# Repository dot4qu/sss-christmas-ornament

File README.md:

# sss-christmas-ornament

A donut-shaped christmas ornament to share with friends and family in 2022. Hardware designed in KiCad, firmware written with Arduino framework and flashed over AVR UPDI interface.

More information in the writeup [here](https://brian.team/art/ornament-2022/).

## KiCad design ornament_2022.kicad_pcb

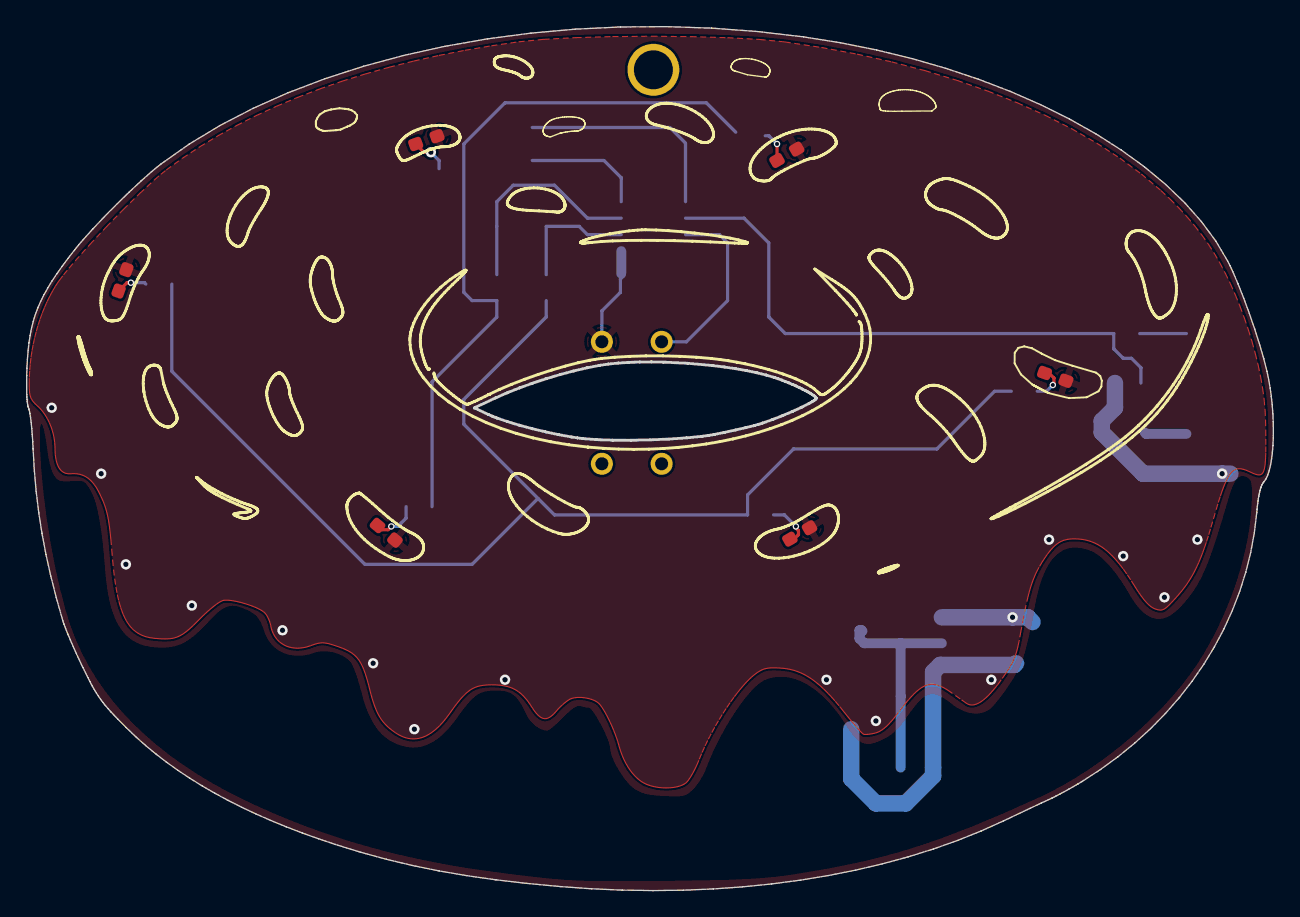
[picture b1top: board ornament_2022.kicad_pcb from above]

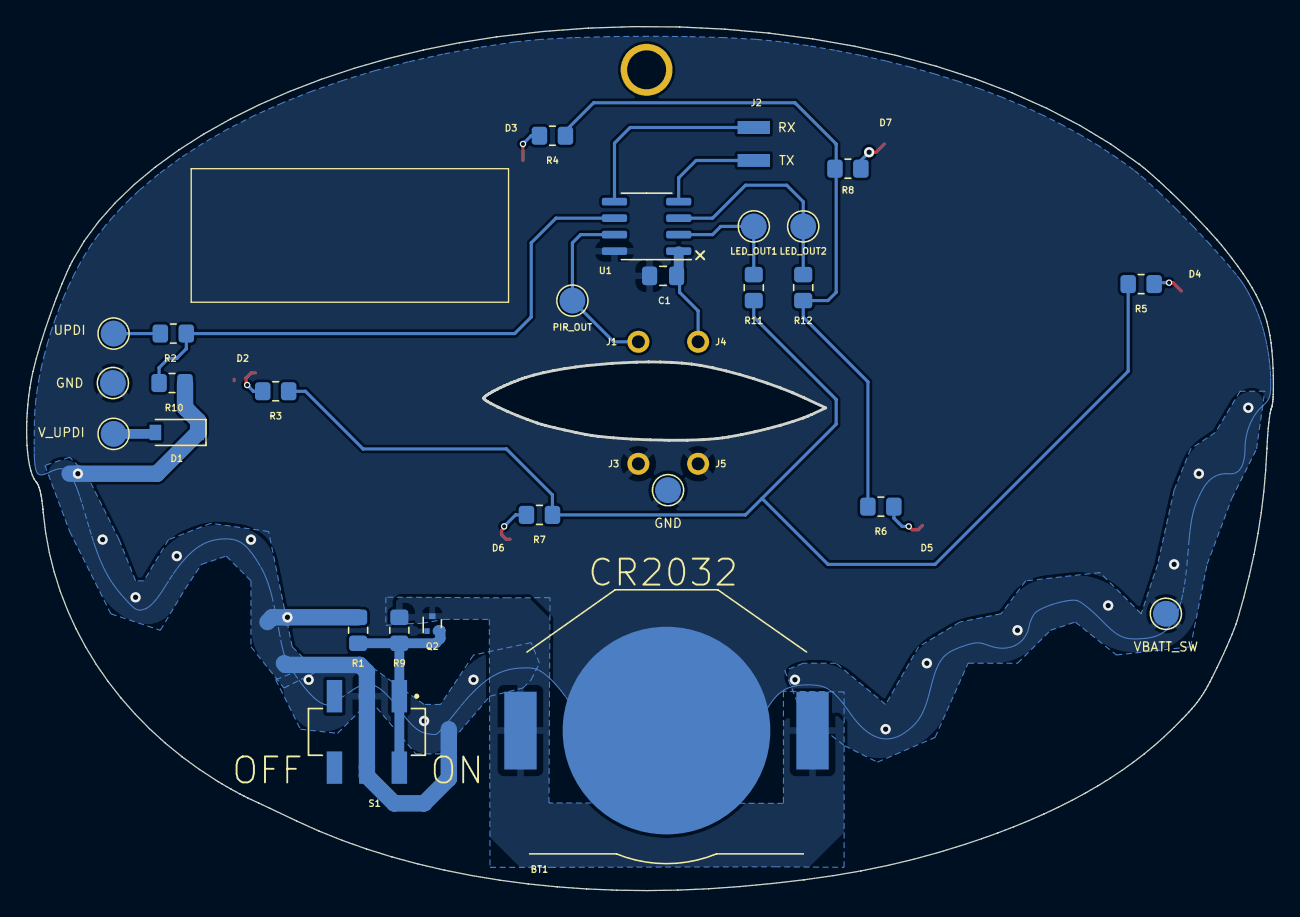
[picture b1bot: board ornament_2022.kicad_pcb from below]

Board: 2 copper layers, 95.9 x 66.4 mm, 37 parts (31 on the bottom side), 20 nets.

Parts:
BT1: CR2032; BatteryHolder_AdamTech_BH-67D-5_1x2032
C1: 0.1uF; C_0805_2012Metric_Pad1.18x1.45mm_HandSolder
D1: 1N4148W; D_SOD-123
D2, D3, D4, D5, D6, D7: LED; LED_0603_1608Metric_Pad1.05x0.95mm_HandSolder
J1: Conn_01x01; PinHeader_1x01_P2.54mm_Vertical
J2: Conn_01x02_Male; Harwin_M20-89003xx_1x02_P2.54mm_Horizontal
J3: GND; PinHeader_1x01_P2.54mm_Vertical
J4: V_PIR; PinHeader_1x01_P2.54mm_Vertical
J5: PIR_TIME; PinHeader_1x01_P2.54mm_Vertical
Q2: Q_PMOS_DGS; SOT-723
R1, R9, R11, R12: 0; R_0805_2012Metric_Pad1.20x1.40mm_HandSolder
R2: 470; R_0805_2012Metric_Pad1.20x1.40mm_HandSolder
R3, R4, R5, R6, R7, R8: 8.2k; R_0805_2012Metric_Pad1.20x1.40mm_HandSolder
R10: 10k; R_0805_2012Metric_Pad1.20x1.40mm_HandSolder
S1: JS202011SCQN; SW_JS202011SCQN
TP1: PIR_OUT; TestPoint_Pad_D2.0mm
TP2: VBATT_SW; TestPoint_Pad_D2.0mm
TP3: LED_OUT1; TestPoint_Pad_D2.0mm
TP4: LED_OUT2; TestPoint_Pad_D2.0mm
TP5, TP8: GND; TestPoint_Pad_D2.0mm
TP6: V_UPDI; TestPoint_Pad_D2.0mm
TP7: UPDI; TestPoint_Pad_D2.0mm
U1: ATtiny412-SS; SOIC-8_3.9x4.9mm_P1.27mm

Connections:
+BATT: BT1.1 (+), Q2.3 (D), R9.1
/LED_OUT1: R11.1, TP3.1, U1.2 (PA6)
/LED_OUT2: R12.1, TP4.1, U1.3 (PA7)
/PIR_OUT: J1.1, TP1.1, U1.7 (PA3)
/RX: J2.2, U1.5 (PA2)
/TX: J2.1, U1.4 (PA1)
/UPDI: R2.2, TP7.1
/V_UPDI: D1.2 (A), TP6.1
GND: BT1.2 (-), C1.2, J3.1, J5.1, Q2.1 (G), TP5.1, TP8.1, U1.8 (GND)
unnamed: D2.1 (K), R3.1
unnamed: D3.1 (K), R4.1
unnamed: D4.1 (K), R5.1
unnamed: D5.1 (K), R6.1
unnamed: D6.1 (K), R7.1
unnamed: D7.1 (K), R8.1
unnamed: Q2.2 (S), R1.1, R9.2, S1.1, S1.4
unnamed: R2.1, R10.1, U1.6 (~RESET/PA0)
unnamed: R3.2, R5.2, R7.2, R11.2
unnamed: R4.2, R6.2, R8.2, R12.2
VBATT_SW: C1.1, D1.1 (K), D2.2 (A), D3.2 (A), D4.2 (A), D5.2 (A), D6.2 (A), D7.2 (A), J4.1, R1.2, R10.2, S1.2, S1.5, TP2.1, U1.1 (VCC)

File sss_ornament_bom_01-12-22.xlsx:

Designator | Package | Quantity | Designation | Supplier and ref
D7,D5,D2,D6,D4,D3 | LED_0603_1608Metric_Pad1.05x0.95mm_HandSolder | 6 | LED | https://www.digikey.de/en/products/detail/würth-elektronik/1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
R2 | R_0805_2012Metric_Pad1.20x1.40mm_HandSolder | 1 | 470 | https://www.digikey.de/en/products/detail/yageo/RC0805JR-074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
R12,R11,R1,R9 | R_0805_2012Metric_Pad1.20x1.40mm_HandSolder | 4 | 0 | https://www.digikey.de/en/products/detail/stackpole-electron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
R8,R7,R6,R4,R3,R5 | R_0805_2012Metric_Pad1.20x1.40mm_HandSolder | 6 | 8.2k | https://www.digikey.de/en/products/detail/yageo/RC0805FR-078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
R10 | R_0805_2012Metric_Pad1.20x1.40mm_HandSolder | 1 | 10k | https://www.digikey.de/en/products/detail/stackpole-electron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
C1 | C_0805_2012Metric_Pad1.18x1.45mm_HandSolder | 1 | 0.1uF | https://www.digikey.de/en/products/detail/samsung-electro-me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
Q2 | SOT-723 | 1 | Q_PMOS_DGS | https://www.digikey.de/en/products/detail/toshiba-semiconduc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
D1 | D_SOD-123 | 1 | 1N4148W | https://www.digikey.de/en/products/detail/smc-diode-solution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
U1 | SOIC-8_3.9x4.9mm_P1.27mm | 1 | ATtiny412-SS | https://www.digikey.de/en/products/detail/microchip-technolo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
BT1 | BatteryHolder_AdamTech_BH-67D-5_1x2032 | 1 | CR2032 | https://www.digikey.de/en/products/detail/adam-tech/BH-67D-5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
S1 | SW_JS202011SCQN | 1 | JS202011SCQN | https://www.digikey.de/en/products/detail/c-k/JS202011SCQN/2094299

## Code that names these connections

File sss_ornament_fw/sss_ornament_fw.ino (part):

#include <avr/sleep.h>

#define LED0_OUT PIN_PA6
#define LED1_OUT PIN_PA7
#define PIR_IN PIN_PA3

#define SLEEP_TIMEOUT_MIN (30)
#define SLEEP_TIMEOUT_MS (1000UL * 60 * SLEEP_TIMEOUT_MIN)
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    triple_flash_pin = LED0_OUT;
  }
  
  // Set up interrupt on PIR pin. Must be BOTHEDGES or LEVEL since we're using a partially-async pin. If using PA2
  // or PA6 (fully async), can wake from deep sleep with any trigger.
  PORTA.PIN3CTRL = (PORTA.PIN3CTRL & ~PORT_ISC_gm) | PORT_ISC_BOTHEDGES_gc | PORT_PULLUPEN_bm;
  
  sei();
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
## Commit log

2023-01-01 Push of rev 1.0 kicad design files, firmware, and BOM
2023-01-01 remove backups dir from git tree
